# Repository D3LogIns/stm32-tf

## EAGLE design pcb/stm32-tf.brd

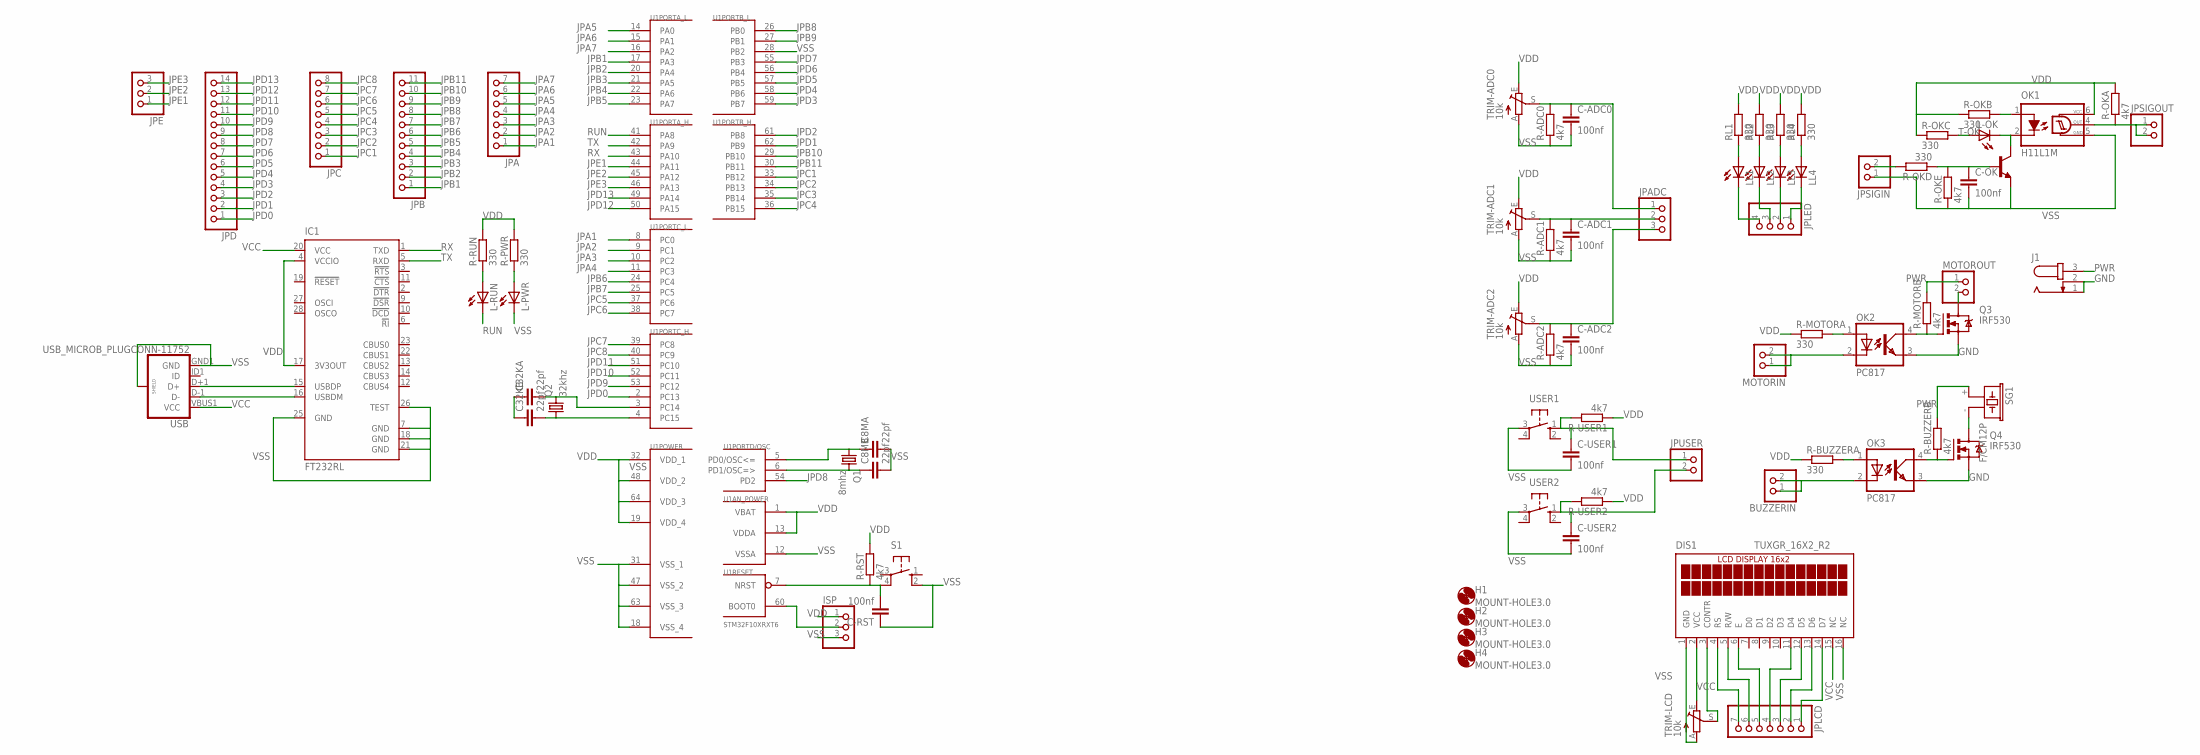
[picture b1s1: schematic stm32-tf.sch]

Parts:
BUZZERIN: PINHD-1X2; 1X02
C8MA, C8MB, C32KA, C32KB: 22pf; C1206
C-ADC0, C-ADC1, C-ADC2: 100nf; C1206
C-OK: 100nf; C1206
C-RST: 100nf; C1206
C-USER1, C-USER2: 100nf; C1206
DIS1: TUXGR_16X2_R2
H1, H2, H3, H4: MOUNT-HOLE3.0; 3,0
IC1: FT232RL; SSOP28
ISP: PINHD-1X3; 1X03
J1: JACK-PLUG0; SPC4077
JPA: PINHD-1X7; 1X07
JPADC: PINHD-1X3; 1X03
JPB: PINHD-1X11; 1X11
JPC: PINHD-1X8; 1X08
JPD: PINHD-1X14; 1X14
JPE: PINHD-1X3; 1X03
JPLCD: PINHD-1X7; 1X07
JPLED: PINHD-1X4; 1X04
JPSIGIN: PINHD-1X2; 1X02
JPSIGOUT: PINHD-1X2; 1X02
JPUSER: PINHD-1X2; 1X02
L-OK: LEDSML1206; SML1206
L-PWR: LEDSML1206; SML1206
L-RUN: LEDSML1206; SML1206
LL1, LL2, LL3, LL4: LEDSML1206; SML1206
MOTORIN: PINHD-1X2; 1X02
MOTOROUT: PINHD-1X2; 1X02
OK1: H11L1M; DIL06
OK2, OK3: PC817; DIL04
Q1: 8mhz; HC49U-V
Q2: 32khz; TC38H
Q3, Q4: IRF530; TO220BV
R-ADC0, R-ADC1, R-ADC2: 4k7; R1206
R-BUZZERA: 330; R1206
R-BUZZERB: 4k7; R1206
R-MOTORA: 330; R1206
R-MOTORB: 4k7; R1206
R-OKA: 4k7; R1206
R-OKB: 330; R1206
R-OKC: 330; R1206
R-OKD: 330; R1206
R-OKE: 4k7; R1206
R-PWR: 330; R1206
R-RST: 4k7; R1206
R-RUN: 330; R1206
R-USER1, R-USER2: 4k7; R1206
RL1, RL2, RL3, RL4: 330; R1206
S1: 10-XX; B3F-10XX
SG1: F/CM12P
T-OK: 2N3904-NPN-TO92-EBC; TO92-EBC
TRIM-ADC0, TRIM-ADC1, TRIM-ADC2: 10k; CA6V
TRIM-LCD: 10k; CA6V
U1: STM32F10XRXT6; TQFP64
USB: USB_MICROB_PLUGCONN-11752; USB-B-MICRO-SMD_V03
USER1, USER2: 10-XX; B3F-10XX

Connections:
GND: J1.1, J1.2, OK2.3 (EMIT), OK3.3 (EMIT), Q3.S, Q4.S
JPA1: JPA.1, U1.8 (PC0)
JPA2: JPA.2, U1.9 (PC1)
JPA3: JPA.3, U1.10 (PC2)
JPA4: JPA.4, U1.11 (PC3)
JPA5: JPA.5, U1.14 (PA0)
JPA6: JPA.6, U1.15 (PA1)
JPA7: JPA.7, U1.16 (PA2)
JPB1: JPB.1, U1.17 (PA3)
JPB2: JPB.2, U1.20 (PA4)
JPB3: JPB.3, U1.21 (PA5)
JPB4: JPB.4, U1.22 (PA6)
JPB5: JPB.5, U1.23 (PA7)
JPB6: JPB.6, U1.24 (PC4)
JPB7: JPB.7, U1.25 (PC5)
JPB8: JPB.8, U1.26 (PB0)
JPB9: JPB.9, U1.27 (PB1)
JPB10: JPB.10, U1.29 (PB10)
JPB11: JPB.11, U1.30 (PB11)
JPC1: JPC.1, U1.33 (PB12)
JPC2: JPC.2, U1.34 (PB13)
JPC3: JPC.3, U1.35 (PB14)
JPC4: JPC.4, U1.36 (PB15)
JPC5: JPC.5, U1.37 (PC6)
JPC6: JPC.6, U1.38 (PC7)
JPC7: JPC.7, U1.39 (PC8)
JPC8: JPC.8, U1.40 (PC9)
JPD0: JPD.1, U1.2 (PC13)
JPD1: JPD.2, U1.62 (PB9)
JPD2: JPD.3, U1.61 (PB8)
JPD3: JPD.4, U1.59 (PB7)
JPD4: JPD.5, U1.58 (PB6)
JPD5: JPD.6, U1.57 (PB5)
JPD6: JPD.7, U1.56 (PB4)
JPD7: JPD.8, U1.55 (PB3)
JPD8: JPD.9, U1.54 (PD2)
JPD9: JPD.10, U1.53 (PC12)
JPD10: JPD.11, U1.52 (PC11)
JPD11: JPD.12, U1.51 (PC10)
JPD12: JPD.13, U1.50 (PA15)
JPD13: JPD.14, U1.49 (PA14)
JPE1: JPE.1, U1.44 (PA11)
JPE2: JPE.2, U1.45 (PA12)
JPE3: JPE.3, U1.46 (PA13)
unnamed: C8MB.1, Q1.2, U1.6 (PD1/OSC=>)
unnamed: C-ADC0.1, JPADC.1, R-ADC0.2, TRIM-ADC0.S
unnamed: C32KB.2, Q2.1, U1.4 (PC15)
unnamed: C32KA.2, Q2.2, U1.3 (PC14)
unnamed: C-RST.2, R-RST.1, S1.4 (P1), U1.7 (NRST)
unnamed: ISP.2, U1.60 (BOOT0)
unnamed: C8MA.1, Q1.1, U1.5 (PD0/OSC<=)
unnamed: L-RUN.A, R-RUN.1
unnamed: IC1.16 (USBDM), USB.D-1 (D-)
unnamed: IC1.15 (USBDP), USB.D+1 (D+)
unnamed: C-ADC1.1, JPADC.2, R-ADC1.2, TRIM-ADC1.S
unnamed: C-ADC2.1, JPADC.3, R-ADC2.2, TRIM-ADC2.S
unnamed: L-PWR.A, R-PWR.1
unnamed: LL1.A, RL1.1
unnamed: JPLED.4, LL1.C
unnamed: LL2.A, RL2.1
unnamed: JPLED.3, LL2.C
unnamed: LL3.A, RL3.1
unnamed: JPLED.2, LL3.C
unnamed: LL4.A, RL4.1
unnamed: JPLED.1, LL4.C
unnamed: C-USER1.1, JPUSER.1, R-USER1.2, USER1.1 (S)
unnamed: C-USER2.1, JPUSER.2, R-USER2.2, USER2.1 (S)
unnamed: C-OK.1, R-OKD.1, R-OKE.2, T-OK.B
unnamed: JPSIGIN.2, R-OKD.2
unnamed: OK2.1 (A), R-MOTORA.2
unnamed: L-OK.C, OK1.2 (C), T-OK.C
unnamed: L-OK.A, R-OKC.2
unnamed: MOTORIN.1, MOTORIN.2, OK2.2 (C)
unnamed: JPSIGOUT.1, JPSIGOUT.2, OK1.4 (OUT), R-OKA.1
unnamed: OK1.1 (A), R-OKB.2
unnamed: OK2.4 (COL), Q3.G, R-MOTORB.1
unnamed: OK3.1 (A), R-BUZZERA.2
unnamed: MOTOROUT.2, Q3.D
unnamed: BUZZERIN.1, BUZZERIN.2, OK3.2 (C)
unnamed: OK3.4 (COL), Q4.G, R-BUZZERB.1
unnamed: Q4.D, SG1.- (2)
unnamed: DIS1.4 (RS), JPLCD.7
unnamed: DIS1.3 (CONTR), TRIM-LCD.S
unnamed: DIS1.5 (R/W), JPLCD.6
unnamed: DIS1.6 (E), JPLCD.5
unnamed: DIS1.11 (D4), JPLCD.4
unnamed: DIS1.12 (D5), JPLCD.3
unnamed: DIS1.13 (D6), JPLCD.2
unnamed: DIS1.14 (D7), JPLCD.1
PWR: J1.3, MOTOROUT.1, R-BUZZERB.2, R-MOTORB.2, SG1.+ (1)
RUN: L-RUN.C, U1.41 (PA8)
RX: IC1.1 (TXD), U1.43 (PA10)
TX: IC1.5 (RXD), U1.42 (PA9)
VCC: DIS1.2 (VCC), DIS1.15 (NC), IC1.20 (VCC), TRIM-LCD.E, USB.VBUS1 (VCC)
VDD: IC1.4 (VCCIO), IC1.17 (3V3OUT), ISP.1, OK1.6 (VCC), R-BUZZERA.1, R-MOTORA.1, R-OKA.2, R-OKB.1, R-OKC.1, R-PWR.2, R-RST.2, R-RUN.2, R-USER1.1, R-USER2.1, RL1.2, RL2.2, RL3.2, RL4.2, TRIM-ADC0.E, TRIM-ADC1.E, TRIM-ADC2.E, U1.1 (VBAT), U1.13 (VDDA), U1.19 (VDD_4), U1.32 (VDD_1), U1.48 (VDD_2), U1.64 (VDD_3)
VSS: C8MA.2, C8MB.2, C32KA.1, C32KB.1, C-ADC0.2, C-ADC1.2, C-ADC2.2, C-OK.2, C-RST.1, C-USER1.2, C-USER2.2, DIS1.1 (GND), DIS1.16 (NC), IC1.7 (GND), IC1.18 (GND), IC1.21 (GND), IC1.25 (GND), IC1.26 (TEST), ISP.3, JPSIGIN.1, L-PWR.C, OK1.5 (GND), R-ADC0.1, R-ADC1.1, R-ADC2.1, R-OKE.1, S1.2 (S1), T-OK.E, TRIM-ADC0.A, TRIM-ADC1.A, TRIM-ADC2.A, TRIM-LCD.A, U1.12 (VSSA), U1.18 (VSS_4), U1.28 (PB2), U1.31 (VSS_1), U1.47 (VSS_2), U1.63 (VSS_3), USB.GND1 (GND), USB.SHIELD1 (SHIELD), USB.SHIELD2 (SHIELD), USB.SHIELD3 (SHIELD), USER1.3, USER2.3

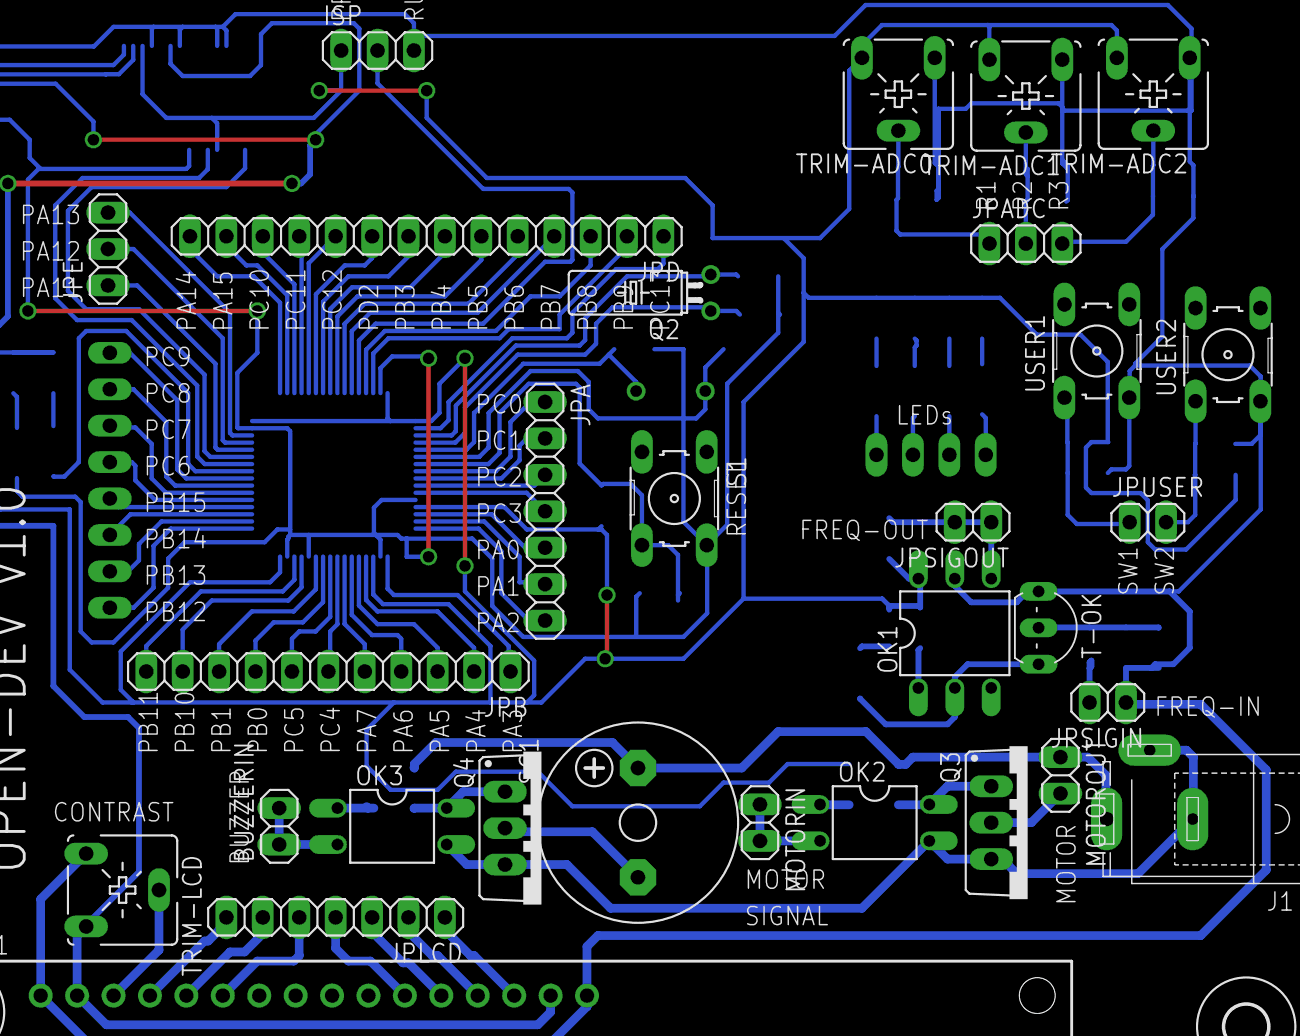
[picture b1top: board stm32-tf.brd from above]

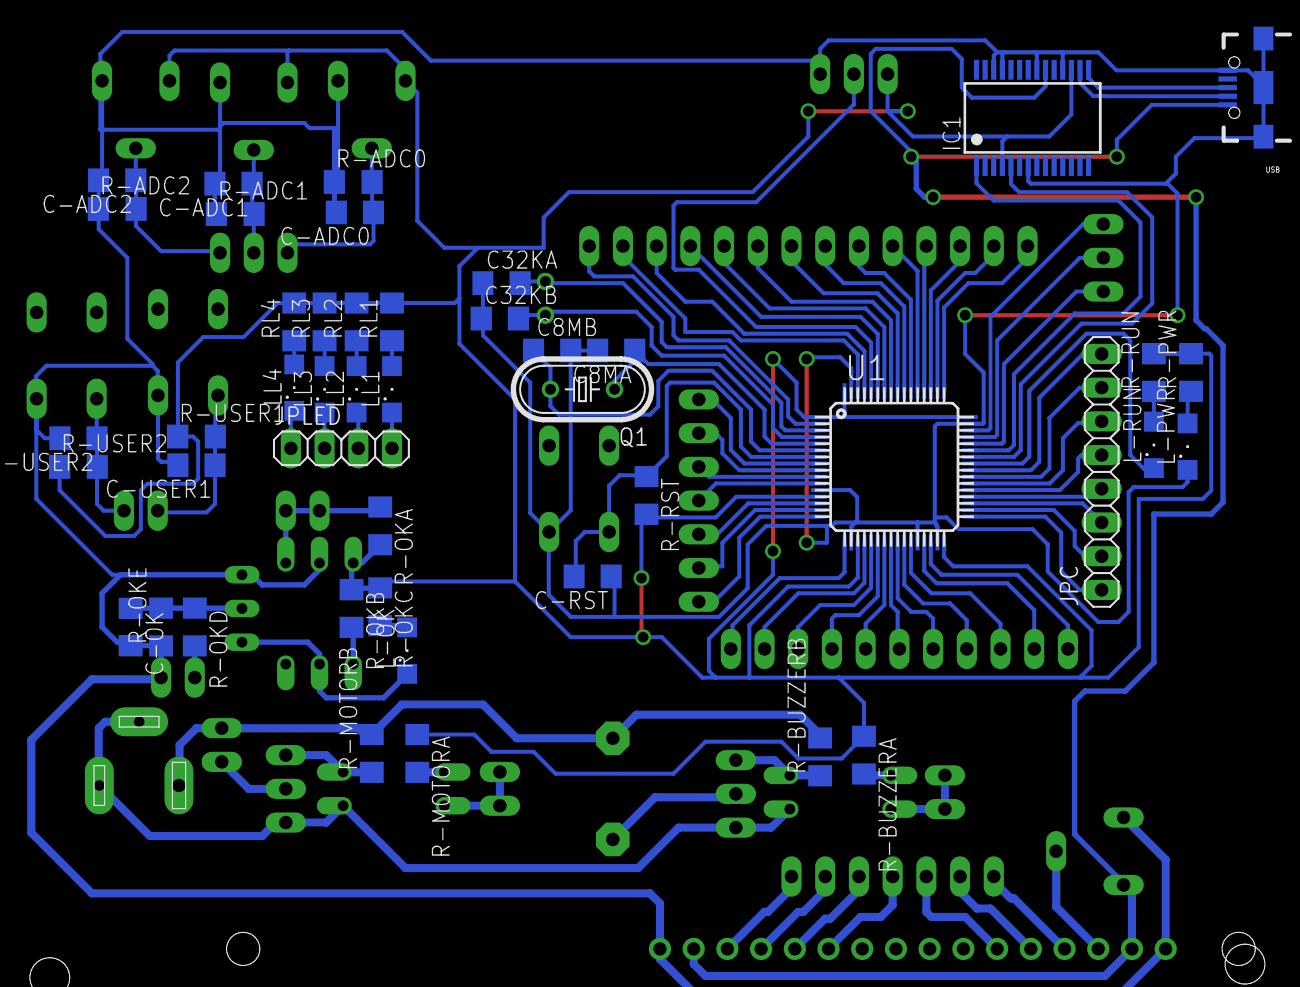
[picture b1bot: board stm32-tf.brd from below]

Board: 2 copper layers, 79 parts (45 on the bottom side), 96 nets.

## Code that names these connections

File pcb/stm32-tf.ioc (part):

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Mcu.Name=STM32F103R(8-B)Tx
Mcu.Package=LQFP64
PA10.Mode=Asynchronous
PA10.Signal=USART1_RX
PA8.Signal=GPIO_Output
PA9.Mode=Asynchronous
PA9.Signal=USART1_TX
PB2.Mode=Event-Out
PB2.Signal=CORTEX_EVENT_OUT
PC14-OSC32_IN.Mode=LSE-External-Oscillator
PC14-OSC32_IN.Signal=SYS_OSC32_IN
PC15-OSC32_OUT.Mode=LSE-External-Oscillator
PC15-OSC32_OUT.Signal=SYS_OSC32_OUT
PD0-OSC_IN.Mode=HSE-External-Oscillator
PD0-OSC_IN.Signal=SYS_OSC_IN
PD1-OSC_OUT.Mode=HSE-External-Oscillator
PD1-OSC_OUT.Signal=SYS_OSC_OUT

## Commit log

2015-02-11 firmware unstable
2015-02-11 estimasi harga
2015-02-11 necessary software
2015-02-11 daftar fitur
2015-02-27 list
2015-03-06 revisi PCB : overlap jalur clock dan microUSB butuh tambahan pad solder
2015-03-10 ready to next stage
2015-03-10 tools tambahan
2015-03-10 tambahan daftar dan driver ftdi
2015-03-10 chibiOS
2015-03-12 Fitur ICU (unstable)

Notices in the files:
parts and their libraries:
SparkFun-Connectors: Licensing: Creative Commons ShareAlike 4.0 International - https://creativecommons.org/licenses/by-sa/4.0
